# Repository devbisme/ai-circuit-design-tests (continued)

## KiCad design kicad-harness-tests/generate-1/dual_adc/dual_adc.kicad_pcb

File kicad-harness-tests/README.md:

# kicad-harness — tests

## Tool under test

[kicad-harness](https://github.com/zxkmm/kicad-harness) is an Agent Skill plus a Python CLI, `kh`.
It has no MCP server and no LLM of its own; Claude Code reads the skill and runs `kh` from Bash.

- **The skill** (`SKILL.md`, `docs/`) sets the working rules: look up every library id, render
  every placement and look at the PNG, write schematics as `.kicad_sch` text, check with
  DRC/ERC, and generate missing footprints from datasheets. It also tells the agent to fix,
  commit and push the skill repo itself when it finds something wrong.
- **`kh`**, all output JSON:
  - Libraries: `sym` (search, pin numbers/coordinates, raw symbol body), `fp`, `validate`.
  - Queries: `info`, `ls` (positions, bounding boxes), `nets`, `netlist`, `bom`.
  - Renders: `view` (any board region or layer set → PNG), `sview` (schematic sheets → PNG).
  - Checks: `drc` (grouped by type, optional zone refill, schematic parity), `erc`.
  - Generation: `board-from-netlist` (netlist → `.kicad_pcb` with footprints and nets,
    headless), `place` (move footprints in the file), `outline` (rectangular Edge.Cuts).
  - Live (KiCad IPC): `live`, `exec <script.py>` (run kipy scripts against an open PCB editor).
- **Footprints from datasheets** are a documented procedure (`docs/footprints/`) using
  KiCad's wizard templates, not a command.
- **Not included:** a schematic API (schematics are text), an autorouter (the skill documents
  the Specctra DSN/SES bridge to an external router), and ratsnest in renders.

It can both create designs (schematic authoring recipes, `board-from-netlist`, `place`,
`outline`, footprint generation; the README's demo is a TP4056 charger built from scratch) and
review them (`drc`, `erc`, `netlist`, `nets`, `view`/`sview`; "Review your design" is one of
its stated uses). So it is tested as a **hybrid**.

Installation is described in [`setup.md`](setup.md).

- **Version:** commit db4bcdb (2026-10-11), package version 0.1.0, kicad-python 0.8.0.
- **Model:** Claude Opus 5.5 on a Claude Pro plan, Claude Code v2.1.296 (both runs).
- **Backend:** KiCad 10.0.4 (`~/bin/kicad10-root`: `kicad-cli` and the bundled Python 3.11
  `pcbnew`). Library lookups resolve to the KiCad 9.0.9 libraries in `/usr/share/kicad`
  (see `setup.md`).

## Why this tool

- It is a different shape from the MCP servers tested so far: a skill plus a CLI that Claude
  drives from Bash, with no tool-call schema in between.
- It gives the agent eyes: `view`/`sview` render any board region or sheet to a PNG that the
  agent is told to look at after every placement.
- `board-from-netlist`, `place` and `outline` cover the schematic → PCB step headlessly, which
  most of the other tools needed the KiCad GUI for.

## Runs

| Run | What it tests | Prompts | Outcome | Equiv. API cost | Time |
|---|---|---|---|---|---|
| [`analyze-1`](analyze-1/) | **Analysis** and JLCPCB fab outputs for an existing design (Konnect run 2) | 1 (multi-part, [`analysis_prompt.txt`](analyze-1/analysis_prompt.txt)) | ERC 0 errors, DRC 0 errors; 14 ranked findings; Gerbers, BOM, CPL, PNG. Found a `kh drc --refill` bug that reports 856 false violations | $3.02 | ~9 min |
| [`generate-1`](generate-1/) | A **full design** from the dual-ADC requirements | 1, plus 4 "keep going" while Freerouting ran ([`design_prompt.txt`](generate-1/design_prompt.txt)) | 6-sheet schematic and routed 4-layer board. ERC 0 errors, DRC 0 errors / 0 unconnected / 0 parity | $10.87 | ~1 h wall clock (~46 min of Claude working time) |

Each run directory has an `executive_summary.md`; start there. Costs are the equivalent
first-party API price of the tokens used (`claude_cost.txt`), not what the Pro subscription
billed. The findings in both runs have not yet been validated by hand.

### analyze-1: analyzer on an existing design

The input is the KiCad project produced by
[Konnect run 2](../konnect-tests/dual-adc-usb-2/): a 4-layer, 140 × 90 mm dual-channel 12-bit,
10 MS/s ADC board with a USB 2.0 interface (LTC2290 ADC, iCE40HX4K FPGA, SDRAM, FT2232H).
The `.kicad_*` files are unchanged copies; the run checked the board's md5 before and after.
The other tools' analysis runs used the same design.

Prompt: `do what analysis-prompt.txt says.` ([`analysis_prompt.txt`](analyze-1/analysis_prompt.txt)
asks for a design review, JLCPCB Gerbers, BOM and CPL, a dark-gray PCB PNG and an executive
summary.)

Quick look:

- **Checks:** `kh drc` gave 0 errors, 0 unconnected, clean schematic parity and 343 warnings.
  `kh erc` gave 0 errors; 201 of its warnings are a stale global library table and 2 are
  benign pin-type warnings.
- **Review method:** every sheet rendered with `kh sview` and read, `kh netlist` plus a
  pin-by-pin dump of every IC, `kh view` renders, and pcbnew scripts for decoupling distance,
  via-in-pad, layer use, pair lengths and stackup. Three datasheets/app notes were fetched and
  cited (FTDI AN_130, TI LM27762, ADA4817).
- **Findings (14, ranked):**
  - Assembly: no LCSC/MPN fields in the BOM; CPL rotations unverified; four through-hole parts.
  - Architecture: FT2232H channel B (the FPGA flash path) is dead while channel A runs sync
    FIFO; the LM27762 divider values check out but R406/R408 are just under the 50 kΩ minimum
    and PGOOD floats; likely over the USB suspend-current limit.
  - Layout: FPGA decaps 6–18 mm from their pins; the AFE sits over the digital +3V3 plane;
    the charge pump sits between the two AFE channels; 9 vias in the ADC's exposed pad;
    no stackup or net classes, so USB D+/D− impedance is uncontrolled; silkscreen overlaps.
  - A list of items that were checked and found correct (divider compensation, gain chain,
    VOCM, clock pins, VBUS capacitance, etc.).
- **Outputs:** `kh` has no fab export, so Gerbers, drill and CPL came from `kicad-cli` 10; the
  BOM came from `kh bom`. All are reformatted for JLCPCB in `analyze-1/jlcpcb/`.
- **kicad-harness problems found:**
  - `kh drc --refill` copies only `.kicad_pcb` and `.kicad_pro` to a temp directory, so the
    project's `.kicad_dru` rules are lost. Result: 856 false violations (499 clearance, 14
    track width). The skill says to "always use --refill".
  - ERC JSON coordinates are 100× too small (passed through from kicad-cli 10 unscaled).
  - `rsvg-convert` is not installed, so `view`/`sview` fail; an Inkscape shim in the
    scratchpad stood in.
- **Not done on purpose:** SKILL.md tells the agent to commit and push fixes to the skill
  repo. Claude didn't, because the user's rules require permission for any git action.

### generate-1: full design

The prompt is [`design_prompt.txt`](generate-1/design_prompt.txt), identical to the one used
for the other tools' design runs.

Prompts, in sequence in one session:

```
do what design_prompt.txt says.
```
```
keep going        (x4)
```

Claude ended its turn each time it was waiting on Freerouting in the background, so the
"keep going" prompts were needed to make it check progress. It then killed and relaunched
the router with fewer passes and finished the last 12 connections with its own A* router.

Quick look:

- **Design:**
  - Signal path: BNC → 1 MΩ‖15 pF 10:1 compensated attenuator → clamp → OPA810 buffer →
    THS4521 FDA (gain 0.95) → single-pole RC anti-alias filter (4.8 MHz) → LTC2290.
  - Capture and link: iCE40HX4K-TQ144 with an 8 MB IS42S16400J SDRAM (0.2 s at full rate,
    twice the requirement); FT232H in sync-245 FIFO mode; W25Q32 config flash.
  - Power: USB-B, about 256 mA estimated, so USB-C wasn't needed. TLV62569 buck (3.3 V),
    LP5907 (3.0 V), AP2112 (1.2 V), TPS60403 (−5 V).
  - Decisions with options are in the executive summary.
- **Schematic:** root plus 6 sheets (Power, FrontEnd, ADC, FPGA, Memory, USB), 163 parts,
  176 nets.
  - Written as label-based `.kicad_sch` text by Claude's `gen_sch.py` from a Python netlist
    (`design.py`); every symbol, footprint and pin number was looked up with `kh sym --pins`
    and `kh validate`.
  - The kicad-cli netlist matches `design.py` exactly. ERC: 0 errors, 2 warnings (FT232H
    symbol pin types).
- **PCB:** 120 × 88 mm, 4 layers: In1 GND plane, In2 +3V3 plane, signals on F/B.Cu.
  - `kh board-from-netlist` created the board. Claude's scripts did placement (anchors,
    FPGA pin swapping by angle with the pin map fed back to the schematic, greedy decap
    placement), net classes, plane zones and 196 locked fanout vias.
  - Freerouting 2.4.1 on a DSN with the plane nets removed left 12 unrouted; a small grid A*
    (`fix_route.py`) finished them. One net uses a short run on the In2 plane layer.
  - DRC (kicad-cli 10, refilled): 0 errors, 0 unconnected, 0 parity issues, 41 warnings.
  - Track minimum was relaxed to 0.10 mm because Freerouting necked some tracks.
- **Not ready for fab:**
  - FTDI, ADI and Lattice datasheets couldn't be downloaded, so FT232H, LTC2290 and iCE40
    pin wiring is from memory and is labelled that way.
  - ~250 mA draw before USB configuration (limit 100 mA); no load switch on PWREN#.
  - Single-pole anti-aliasing; USB D+/D− not routed as a 90 Ω pair; SDRAM bus not
    length-matched; fixed (not trimmable) probe compensation.
  - No FPGA gateware or host software.
- **kicad-harness / environment problems found:**
  - `kh` library lookups fell back to KiCad 9 libraries, where the USB-B shield pad is named
    `5` instead of `SH`. Fixed with project `sym-lib-table`/`fp-lib-table` files.
  - `rsvg-convert` missing (same Inkscape shim as run 1).
  - KiCad 10 pcbnew SWIG: `BOARD.Tracks()` breaks after `Remove()`, and removing Edge.Cuts
    drawings segfaults.
  - No autorouter in `kh`; the DSN/SES bridge to Freerouting is documented but scripted by
    Claude.
- **Not done on purpose:** no commits to the skill repo, as in run 1.

### Comparison of the two runs

- `kh` did most of the inspection and checking work in both runs, but Claude wrote 16
  Python scripts to do the actual design: schematic writing, placement, routing prep and route
  completion. kicad-harness is closer to a set of instruments than to a design tool.
- The skill's "render it and look" rule was followed in both runs and was useful for
  reviewing placement.
- Both runs found real `kh` bugs (`--refill` losing `.kicad_dru`, ERC coordinate scale) and
  environment gaps that the tool doesn't check for (`rsvg-convert`, stale library tables).

## Layout

```
kicad-harness-tests/
├── README.md                   <- this file
├── setup.md                    <- how kicad-harness was installed and configured
├── analyze-1/                  <- run 1: analysis of the Konnect run-2 design
│   ├── executive_summary.md    <- start here
│   ├── analysis_prompt.txt     <- the prompt
│   ├── claude_transcript.txt   <- the session
│   ├── claude_cost.txt         <- token usage and equivalent API cost
│   ├── session_cost.py         <- script that produced claude_cost.txt
│   ├── dual_adc_usb.kicad_pro, .kicad_pcb, .kicad_dru, .kicad_prl, .kicad_sch
│   ├── afe_a, afe_b, adc, fpga, usb, power .kicad_sch
│   ├── dual_adc_usb_pcb.png    <- PCB render on a dark-gray background
│   └── jlcpcb/                 <- Gerber zip, unzipped gerbers, JLCPCB BOM and CPL
└── generate-1/                 <- run 2: full design from the dual-ADC prompt
    ├── executive_summary.md    <- start here
    ├── design_prompt.txt       <- the prompt
    ├── claude_transcript.txt   <- the session
    ├── claude_cost.txt         <- token usage and equivalent API cost
    ├── session_cost.py         <- script that produced claude_cost.txt
    ├── dual_adc/               <- the KiCad 10 project
    │   ├── dual_adc.kicad_pro, .kicad_pcb, .kicad_prl, .kicad_sch
    │   ├── Power, FrontEnd, ADC, FPGA, Memory, USB .kicad_sch
    │   ├── sym-lib-table, fp-lib-table  <- point at the KiCad 10 libraries
    │   ├── fab/                <- Gerbers, drill, pick-and-place, BOM, schematic PDF
    │   └── renders/            <- board front/back and schematic sheet PNGs
    ├── work/                   <- intermediate boards, DSN/SES, Freerouting log, DRC/ERC
    │                              JSON, renders
    └── scripts/
        ├── circuit.py          <- small netlist DSL (parts, pin->net maps, sheets)
        ├── design.py           <- the netlist: parts, values, footprints, pin->net
        ├── pins.py             <- symbol pin dump via `kh sym --pins`
        ├── pins10.py, fpinfo.py  <- pin and pad dumps read straight from the KiCad 10 libraries
        ├── sexp.py             <- small S-expression reader/writer
        ├── gen_sch.py          <- writes the label-based hierarchical schematic
        ├── verify_netlist.py   <- kicad-cli netlist vs design.py
        ├── place.py, pinmap.json  <- placement and FPGA pin reassignment
        ├── route_prep.py       <- net classes, plane zones, locked fanout, DSN export
        ├── edit_fanout.py      <- one-off fix to a bad GND fanout at U10
        ├── dsn_cut.py          <- removes plane nets from the DSN
        ├── import_ses.py       <- Freerouting SES import, pour refill
        ├── fix_route.py        <- grid A* for the connections Freerouting left
        └── prune.py, polish.py <- dead-end spur removal; outline, holes, silk
```

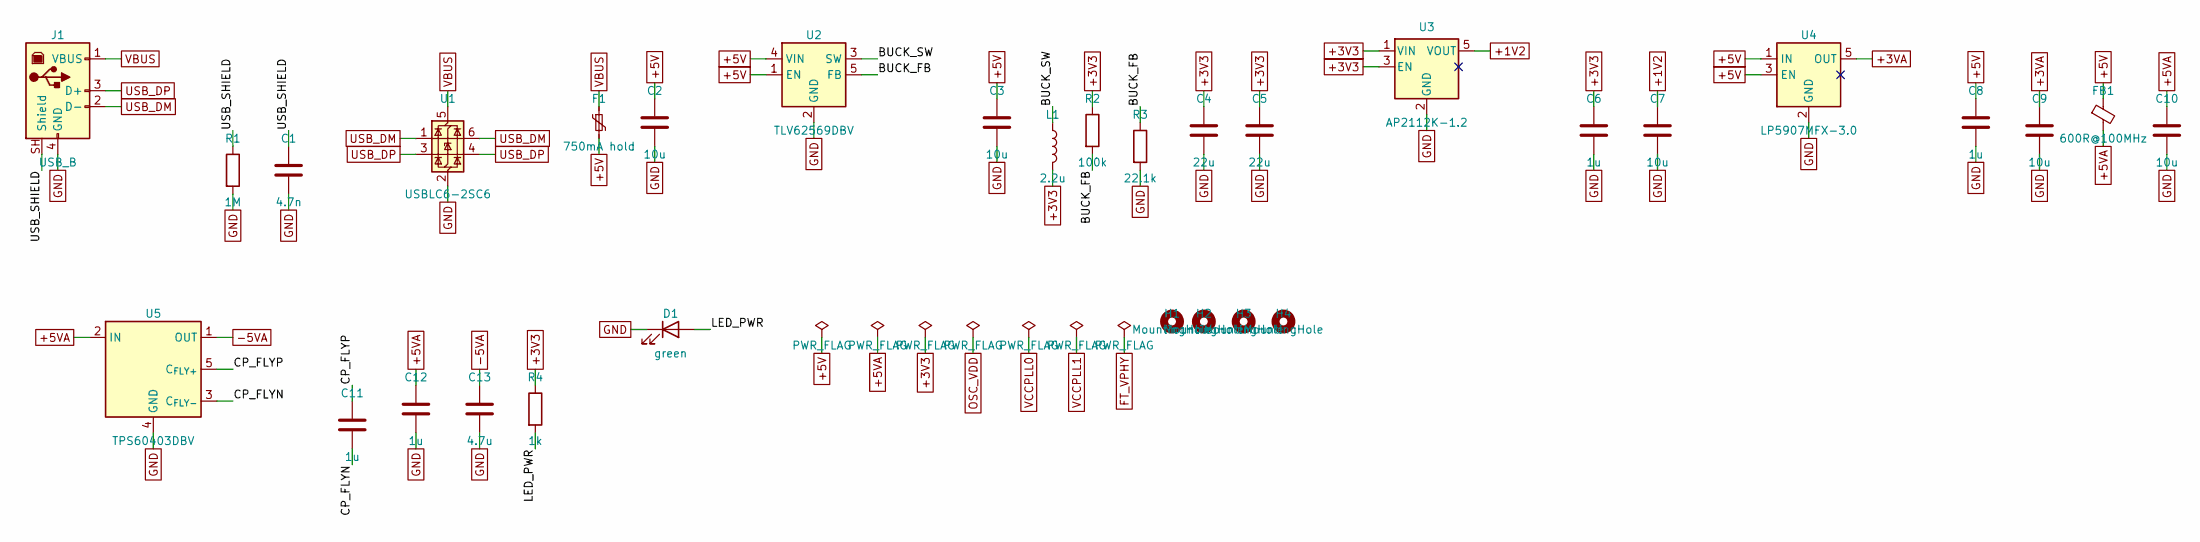
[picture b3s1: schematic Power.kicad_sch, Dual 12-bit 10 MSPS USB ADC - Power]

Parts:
C1: 4.7n; C_0805_2012Metric
C2, C3, C7, C9, C10: 10u; C_0805_2012Metric
C4, C5: 22u; C_0805_2012Metric
C6, C8, C11, C12: 1u; C_0603_1608Metric
C13: 4.7u; C_0805_2012Metric
D1: green; LED_0603_1608Metric
F1: 750mA hold; Fuse_1206_3216Metric
FB1: 600R@100MHz; L_0805_2012Metric
H1, H2, H3, H4: MountingHole; MountingHole_3.2mm_M3
J1: USB_B; USB_B_OST_USB-B1HSxx_Horizontal
L1: 2.2u; L_Bourns-SRN4018
R1: 1M; R_0603_1608Metric
R2: 100k; R_0603_1608Metric
R3: 22.1k; R_0603_1608Metric
R4: 1k; R_0603_1608Metric
U1: USBLC6-2SC6; SOT-23-6
U2: TLV62569DBV; SOT-23-5
U3: AP2112K-1.2; SOT-23-5
U4: LP5907MFX-3.0; SOT-23-5
U5: TPS60403DBV; SOT-23-5

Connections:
+1V2: C7.1, U3.5 (VOUT); also elsewhere on the board
+3V3: C4.1, C5.1, C6.1, L1.2, R2.1, R4.1, U3.1 (VIN), U3.3 (EN); also elsewhere on the board
+3VA: C9.1, U4.5 (OUT); also elsewhere on the board
+5V: C2.1, C3.1, C8.1, F1.2, FB1.1, U2.1 (EN), U2.4 (VIN), U4.1 (IN), U4.3 (EN)
+5VA: C10.1, C12.1, FB1.2, U5.2 (IN); also elsewhere on the board
-5VA: C13.1, U5.1 (OUT); also elsewhere on the board
/Power/BUCK_FB: R2.2, R3.1, U2.5 (FB)
/Power/BUCK_SW: L1.1, U2.3 (SW)
/Power/CP_FLYN: C11.2, U5.3 (C_{FLY-})
/Power/CP_FLYP: C11.1, U5.5 (C_{FLY+})
/Power/LED_PWR: D1.2 (A), R4.2
/Power/USB_SHIELD: C1.1, J1.SH (Shield), R1.1
GND: C1.2, C2.2, C3.2, C4.2, C5.2, C6.2, C7.2, C8.2, C9.2, C10.2, C12.2, C13.2, D1.1 (K), J1.4 (GND), R1.2, R3.2, U1.2 (GND), U2.2 (GND), U3.2 (GND), U4.2 (GND), U5.4 (GND); also elsewhere on the board
USB_DM: J1.2 (D-), U1.1 (I/O1), U1.6 (I/O1); also elsewhere on the board
USB_DP: J1.3 (D+), U1.3 (I/O2), U1.4 (I/O2); also elsewhere on the board
VBUS: F1.1, J1.1 (VBUS), U1.5 (VBUS)

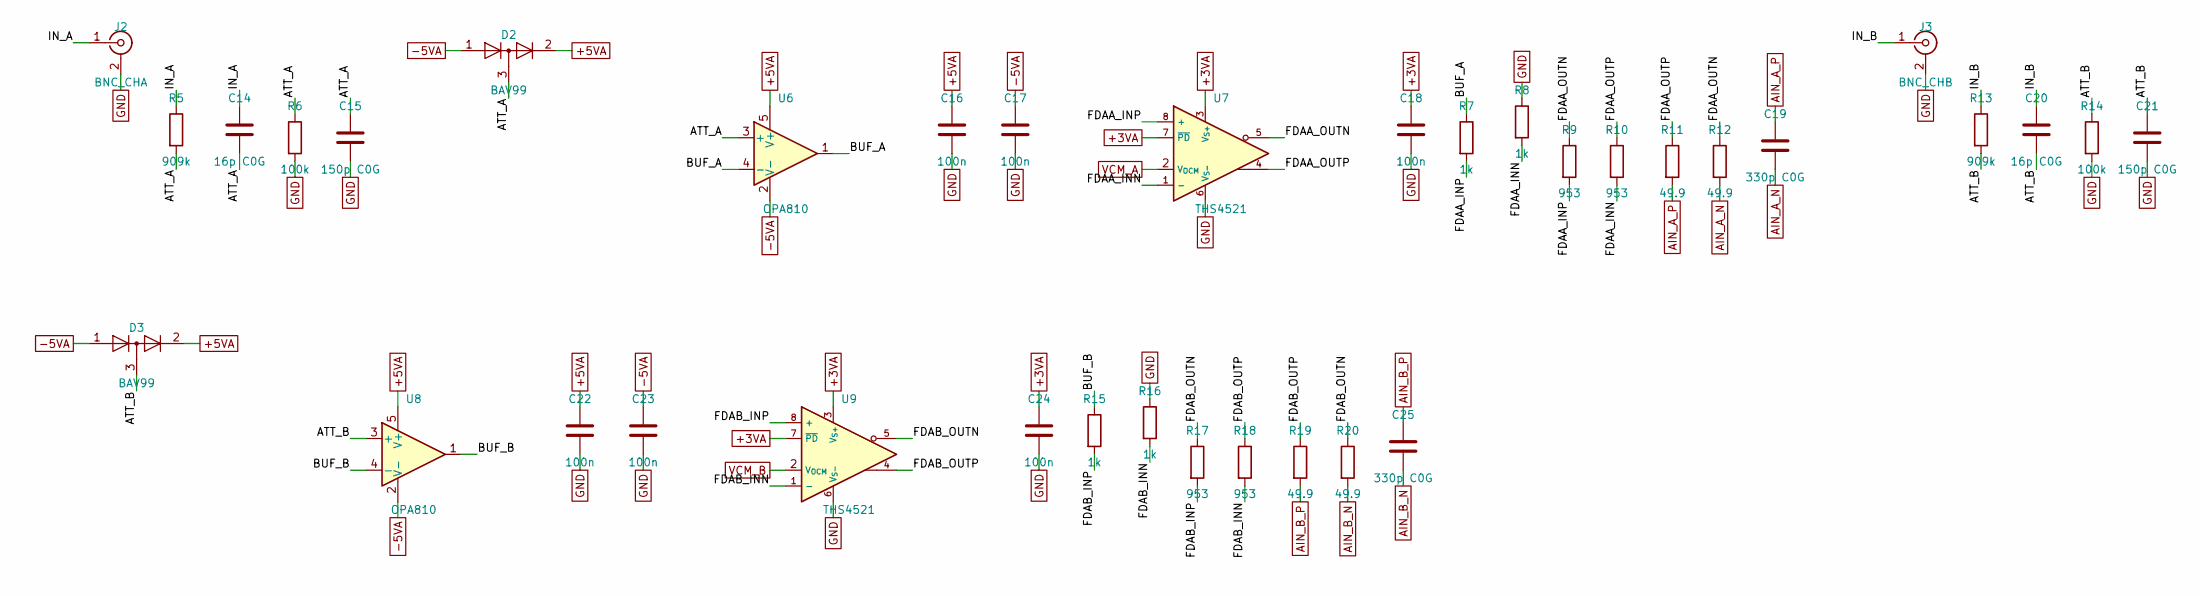
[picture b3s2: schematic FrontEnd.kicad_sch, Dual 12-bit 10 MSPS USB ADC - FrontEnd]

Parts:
C14, C20: 16p C0G; C_1206_3216Metric
C15, C21: 150p C0G; C_0603_1608Metric
C16, C17, C18, C22, C23, C24: 100n; C_0603_1608Metric
C19, C25: 330p C0G; C_0603_1608Metric
D2, D3: BAV99; SOT-23
J2: BNC_CHA; BNC_Amphenol_B6252HB-NPP3G-50_Horizontal
J3: BNC_CHB; BNC_Amphenol_B6252HB-NPP3G-50_Horizontal
R5, R13: 909k; R_1206_3216Metric
R6, R14: 100k; R_0603_1608Metric
R7, R8, R15, R16: 1k; R_0603_1608Metric
R9, R10, R17, R18: 953; R_0603_1608Metric
R11, R12, R19, R20: 49.9; R_0603_1608Metric
U6, U8: OPA810; SOT-23-5
U7, U9: THS4521; SOIC-8_3.9x4.9mm_P1.27mm

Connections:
+3VA: C18.1, C24.1, U7.3 (V_{S+}), U7.7 (~PD), U9.3 (V_{S+}), U9.7 (~PD); also elsewhere on the board
+5VA: C16.1, C22.1, D2.2 (A), D3.2 (A), U6.5 (V+), U8.5 (V+); also elsewhere on the board
-5VA: C17.1, C23.1, D2.1 (K), D3.1 (K), U6.2 (V-), U8.2 (V-); also elsewhere on the board
/FrontEnd/ATT_A: C14.2, C15.1, D2.3 (K), R5.2, R6.1, U6.3 (+)
/FrontEnd/ATT_B: C20.2, C21.1, D3.3 (K), R13.2, R14.1, U8.3 (+)
/FrontEnd/BUF_A: R7.1, U6.1, U6.4 (-)
/FrontEnd/BUF_B: R15.1, U8.1, U8.4 (-)
/FrontEnd/FDAA_INN: R8.2, R10.2, U7.1 (-)
/FrontEnd/FDAA_INP: R7.2, R9.2, U7.8 (+)
/FrontEnd/FDAA_OUTN: R9.1, R12.1, U7.5
/FrontEnd/FDAA_OUTP: R10.1, R11.1, U7.4
/FrontEnd/FDAB_INN: R16.2, R18.2, U9.1 (-)
/FrontEnd/FDAB_INP: R15.2, R17.2, U9.8 (+)
/FrontEnd/FDAB_OUTN: R17.1, R20.1, U9.5
/FrontEnd/FDAB_OUTP: R18.1, R19.1, U9.4
/FrontEnd/IN_A: C14.1, J2.1 (In), R5.1
/FrontEnd/IN_B: C20.1, J3.1 (In), R13.1
AIN_A_N: C19.2, R12.2; also elsewhere on the board
AIN_A_P: C19.1, R11.2; also elsewhere on the board
AIN_B_N: C25.2, R20.2; also elsewhere on the board
AIN_B_P: C25.1, R19.2; also elsewhere on the board
GND: C15.2, C16.2, C17.2, C18.2, C21.2, C22.2, C23.2, C24.2, J2.2 (Ext), J3.2 (Ext), R6.2, R8.1, R14.2, R16.1, U7.6 (V_{S-}), U9.6 (V_{S-}); also elsewhere on the board
VCM_A: U7.2 (V_{OCM}); also elsewhere on the board
VCM_B: U9.2 (V_{OCM}); also elsewhere on the board

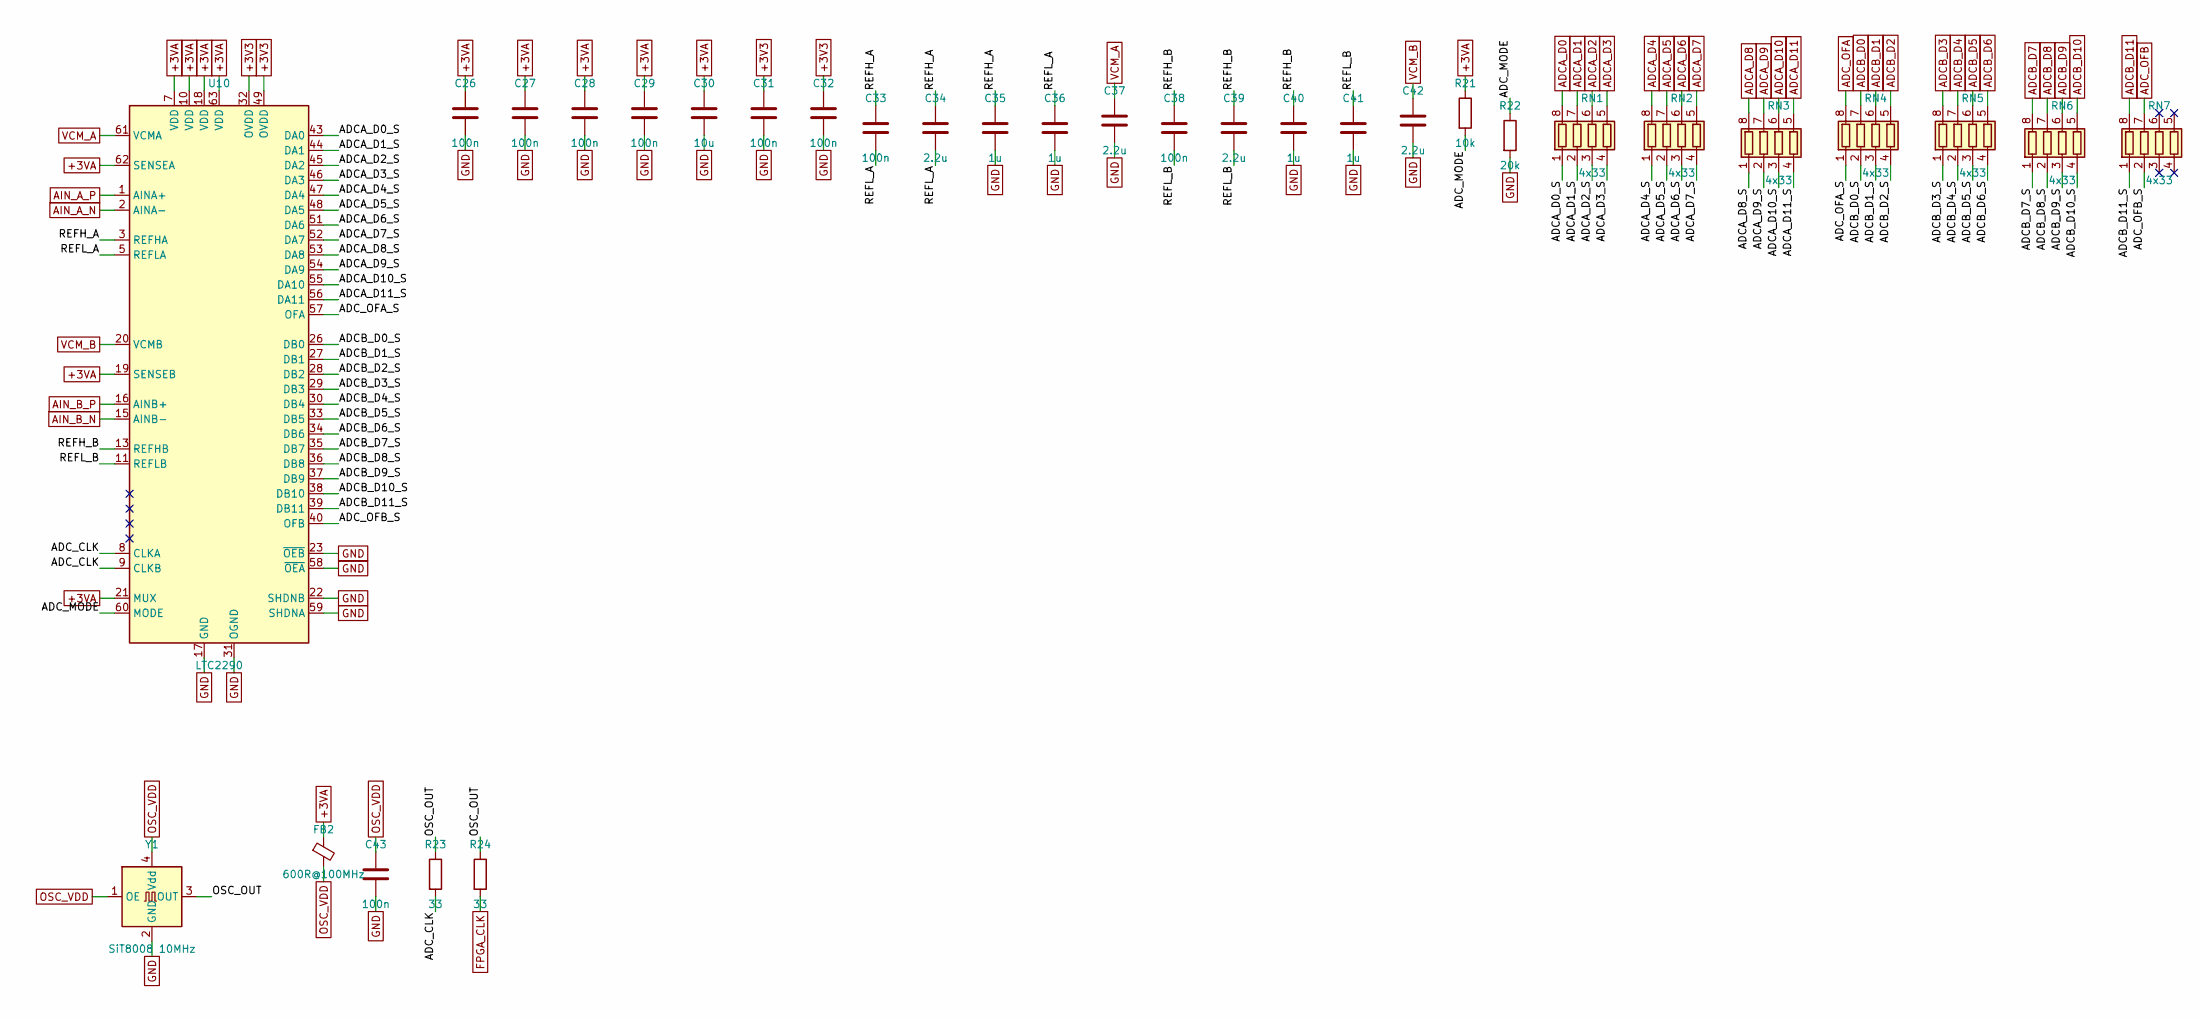
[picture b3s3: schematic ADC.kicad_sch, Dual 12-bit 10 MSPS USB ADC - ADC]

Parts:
C26, C27, C28, C29, C31, C32, C33, C38, C43: 100n; C_0603_1608Metric
C30: 10u; C_0805_2012Metric
C34, C37, C39, C42: 2.2u; C_0603_1608Metric
C35, C36, C40, C41: 1u; C_0603_1608Metric
FB2: 600R@100MHz; L_0805_2012Metric
R21: 10k; R_0603_1608Metric
R22: 20k; R_0603_1608Metric
R23, R24: 33; R_0603_1608Metric
RN1, RN2, RN3, RN4, RN5, RN6, RN7: 4x33; R_Array_Convex_4x0603
U10: LTC2290; QFN-64-1EP_9x9mm_P0.5mm_EP7.15x7.15mm
Y1: SiT8008 10MHz; Oscillator_SMD_SiT_PQFN-4Pin_3.2x2.5mm

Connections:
+3V3: C31.1, C32.1, U10.32 (OVDD), U10.49 (OVDD); also elsewhere on the board
+3VA: C26.1, C27.1, C28.1, C29.1, C30.1, FB2.1, R21.1, U10.7 (VDD), U10.10 (VDD), U10.18 (VDD), U10.19 (SENSEB), U10.21 (MUX), U10.62 (SENSEA), U10.63 (VDD); also elsewhere on the board
/ADC/ADCA_D0_S: RN1.1 (R1.1), U10.43 (DA0)
/ADC/ADCA_D1_S: RN1.2 (R2.1), U10.44 (DA1)
/ADC/ADCA_D2_S: RN1.3 (R3.1), U10.45 (DA2)
/ADC/ADCA_D3_S: RN1.4 (R4.1), U10.46 (DA3)
/ADC/ADCA_D4_S: RN2.1 (R1.1), U10.47 (DA4)
/ADC/ADCA_D5_S: RN2.2 (R2.1), U10.48 (DA5)
/ADC/ADCA_D6_S: RN2.3 (R3.1), U10.51 (DA6)
/ADC/ADCA_D7_S: RN2.4 (R4.1), U10.52 (DA7)
/ADC/ADCA_D8_S: RN3.1 (R1.1), U10.53 (DA8)
/ADC/ADCA_D9_S: RN3.2 (R2.1), U10.54 (DA9)
/ADC/ADCA_D10_S: RN3.3 (R3.1), U10.55 (DA10)
/ADC/ADCA_D11_S: RN3.4 (R4.1), U10.56 (DA11)
/ADC/ADCB_D0_S: RN4.2 (R2.1), U10.26 (DB0)
/ADC/ADCB_D1_S: RN4.3 (R3.1), U10.27 (DB1)
/ADC/ADCB_D2_S: RN4.4 (R4.1), U10.28 (DB2)
/ADC/ADCB_D3_S: RN5.1 (R1.1), U10.29 (DB3)
/ADC/ADCB_D4_S: RN5.2 (R2.1), U10.30 (DB4)
/ADC/ADCB_D5_S: RN5.3 (R3.1), U10.33 (DB5)
/ADC/ADCB_D6_S: RN5.4 (R4.1), U10.34 (DB6)
/ADC/ADCB_D7_S: RN6.1 (R1.1), U10.35 (DB7)
/ADC/ADCB_D8_S: RN6.2 (R2.1), U10.36 (DB8)
/ADC/ADCB_D9_S: RN6.3 (R3.1), U10.37 (DB9)
/ADC/ADCB_D10_S: RN6.4 (R4.1), U10.38 (DB10)
/ADC/ADCB_D11_S: RN7.1 (R1.1), U10.39 (DB11)
/ADC/ADC_CLK: R23.2, U10.8 (CLKA), U10.9 (CLKB)
/ADC/ADC_MODE: R21.2, R22.1, U10.60 (MODE)
/ADC/ADC_OFA_S: RN4.1 (R1.1), U10.57 (OFA)
/ADC/ADC_OFB_S: RN7.2 (R2.1), U10.40 (OFB)
/ADC/OSC_OUT: R23.1, R24.1, Y1.3 (OUT)
/ADC/REFH_A: C33.1, C34.1, C35.1, U10.3 (REFHA), U10.4 (REFHA)
/ADC/REFH_B: C38.1, C39.1, C40.1, U10.13 (REFHB), U10.14 (REFHB)
/ADC/REFL_A: C33.2, C34.2, C36.1, U10.5 (REFLA), U10.6 (REFLA)
/ADC/REFL_B: C38.2, C39.2, C41.1, U10.11 (REFLB), U10.12 (REFLB)
ADCA_D0: RN1.8 (R1.2); also elsewhere on the board
ADCA_D1: RN1.7 (R2.2); also elsewhere on the board
ADCA_D2: RN1.6 (R3.2); also elsewhere on the board
ADCA_D3: RN1.5 (R4.2); also elsewhere on the board
ADCA_D4: RN2.8 (R1.2); also elsewhere on the board
ADCA_D5: RN2.7 (R2.2); also elsewhere on the board
ADCA_D6: RN2.6 (R3.2); also elsewhere on the board
ADCA_D7: RN2.5 (R4.2); also elsewhere on the board
ADCA_D8: RN3.8 (R1.2); also elsewhere on the board
ADCA_D9: RN3.7 (R2.2); also elsewhere on the board
ADCA_D10: RN3.6 (R3.2); also elsewhere on the board
ADCA_D11: RN3.5 (R4.2); also elsewhere on the board
ADCB_D0: RN4.7 (R2.2); also elsewhere on the board
ADCB_D1: RN4.6 (R3.2); also elsewhere on the board
ADCB_D2: RN4.5 (R4.2); also elsewhere on the board
ADCB_D3: RN5.8 (R1.2); also elsewhere on the board
ADCB_D4: RN5.7 (R2.2); also elsewhere on the board
ADCB_D5: RN5.6 (R3.2); also elsewhere on the board
ADCB_D6: RN5.5 (R4.2); also elsewhere on the board
ADCB_D7: RN6.8 (R1.2); also elsewhere on the board
ADCB_D8: RN6.7 (R2.2); also elsewhere on the board
ADCB_D9: RN6.6 (R3.2); also elsewhere on the board
ADCB_D10: RN6.5 (R4.2); also elsewhere on the board
ADCB_D11: RN7.8 (R1.2); also elsewhere on the board
ADC_OFA: RN4.8 (R1.2); also elsewhere on the board
ADC_OFB: RN7.7 (R2.2); also elsewhere on the board
AIN_A_N: U10.2 (AINA-); also elsewhere on the board
AIN_A_P: U10.1 (AINA+); also elsewhere on the board
AIN_B_N: U10.15 (AINB-); also elsewhere on the board
AIN_B_P: U10.16 (AINB+); also elsewhere on the board
FPGA_CLK: R24.2; also elsewhere on the board
GND: C26.2, C27.2, C28.2, C29.2, C30.2, C31.2, C32.2, C35.2, C36.2, C37.2, C40.2, C41.2, C42.2, C43.2, R22.2, U10.17 (GND), U10.22 (SHDNB), U10.23 (~OEB), U10.31 (OGND), U10.50 (OGND), U10.58 (~OEA), U10.59 (SHDNA), U10.64 (GND), U10.65 (GND), Y1.2 (GND); also elsewhere on the board
OSC_VDD: C43.1, FB2.2, Y1.1 (OE), Y1.4 (Vdd)
VCM_A: C37.1, U10.61 (VCMA); also elsewhere on the board
VCM_B: C42.1, U10.20 (VCMB); also elsewhere on the board

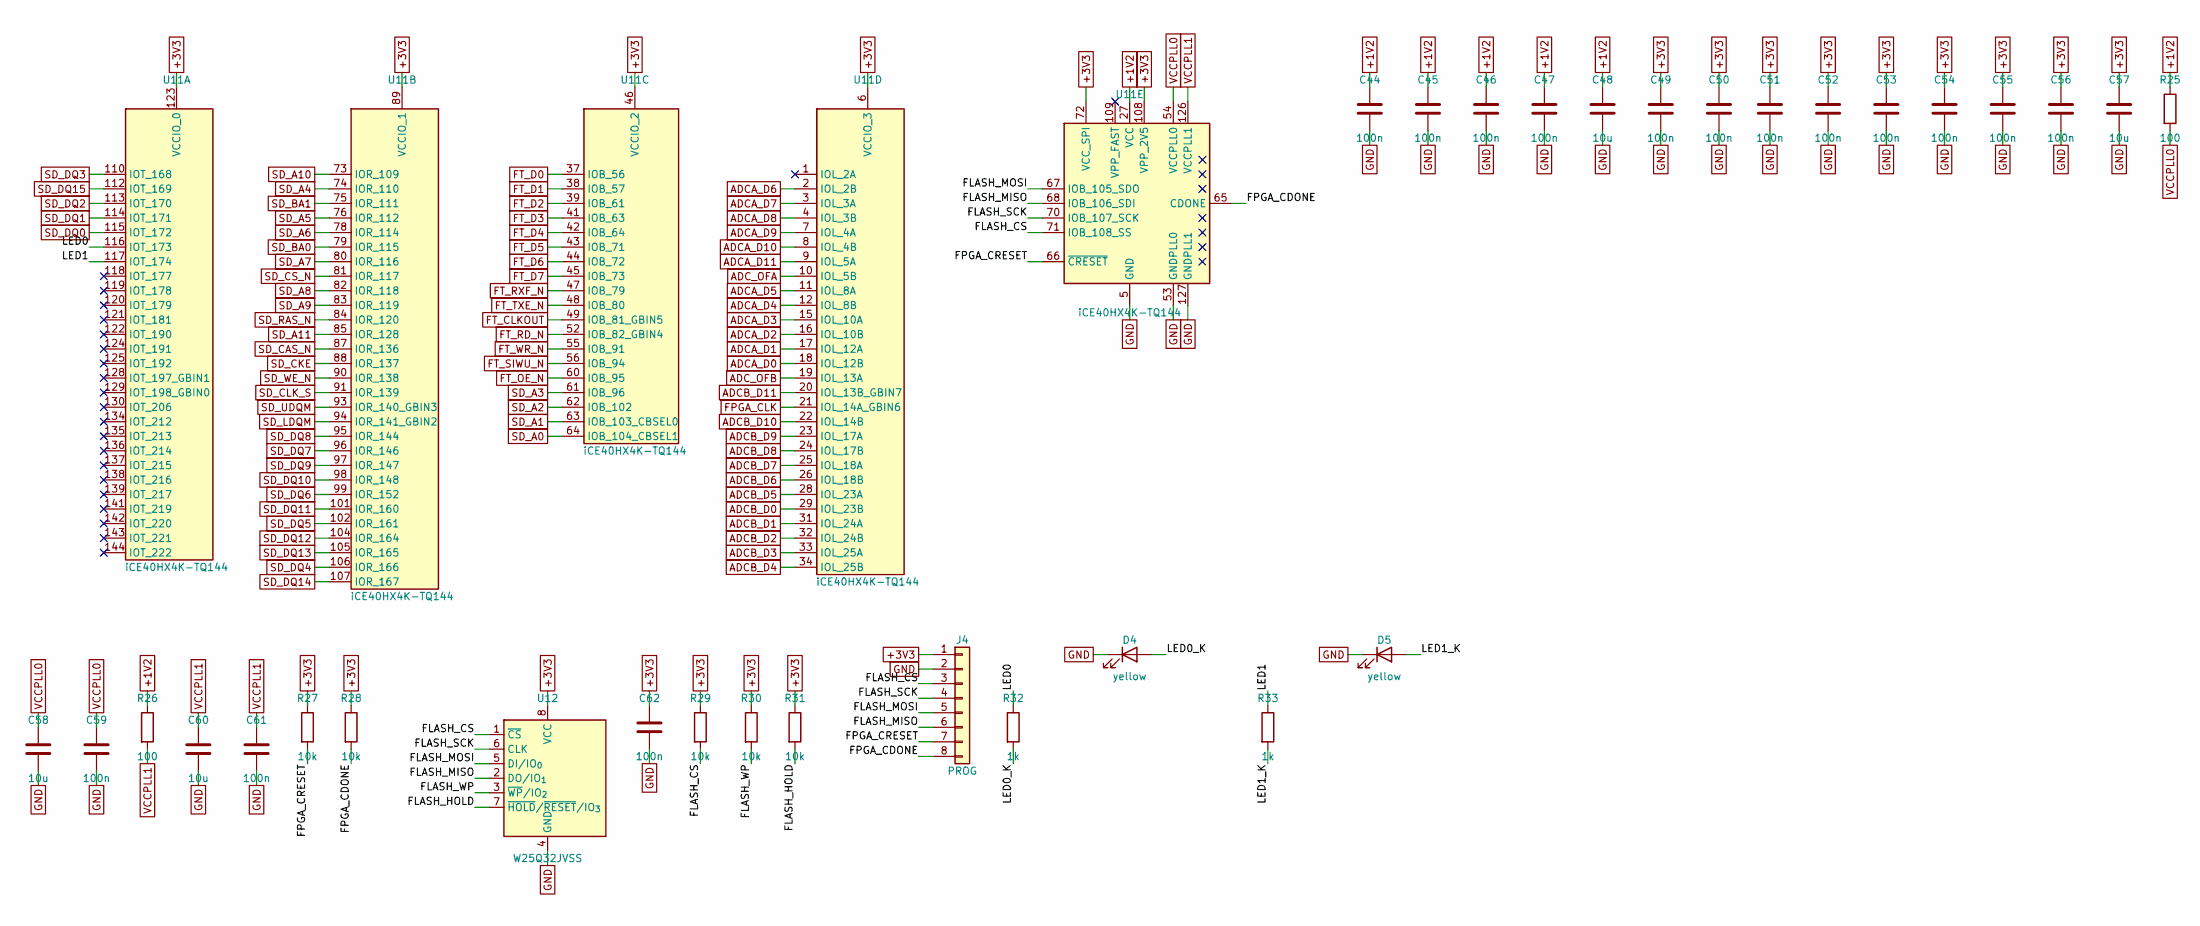
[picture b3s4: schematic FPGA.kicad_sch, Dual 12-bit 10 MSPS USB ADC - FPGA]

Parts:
C44, C45, C46, C47, C49, C50, C51, C52, C53, C54, C55, C56, C59, C61, C62: 100n; C_0603_1608Metric
C48, C57, C58, C60: 10u; C_0805_2012Metric
D4, D5: yellow; LED_0603_1608Metric
J4: PROG; PinHeader_1x08_P2.54mm_Vertical
R25, R26: 100; R_0603_1608Metric
R27, R28, R29, R30, R31: 10k; R_0603_1608Metric
R32, R33: 1k; R_0603_1608Metric
U11: iCE40HX4K-TQ144; TQFP-144_20x20mm_P0.5mm
U12: W25Q32JVSS; SOIC-8_5.3x5.3mm_P1.27mm

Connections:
+1V2: C44.1, C45.1, C46.1, C47.1, C48.1, R25.1, R26.1, U11.27 (VCC), U11.40 (VCC), U11.92 (VCC), U11.111 (VCC); also elsewhere on the board
+3V3: C49.1, C50.1, C51.1, C52.1, C53.1, C54.1, C55.1, C56.1, C57.1, C62.1, J4.1, R27.1, R28.1, R29.1, R30.1, R31.1, U11.6 (VCCIO_3), U11.30 (VCCIO_3), U11.46 (VCCIO_2), U11.57 (VCCIO_2), U11.72 (VCC_SPI), U11.89 (VCCIO_1), U11.100 (VCCIO_1), U11.108 (VPP_2V5), U11.123 (VCCIO_0), U11.131 (VCCIO_0), U12.8 (VCC); also elsewhere on the board
/FPGA/FLASH_CS: J4.3, R29.2, U11.71 (IOB_108_SS), U12.1 (~CS)
/FPGA/FLASH_HOLD: R31.2, U12.7 (~HOLD/~RESET/IO_{3})
/FPGA/FLASH_MISO: J4.6, U11.68 (IOB_106_SDI), U12.2 (DO/IO_{1})
/FPGA/FLASH_MOSI: J4.5, U11.67 (IOB_105_SDO), U12.5 (DI/IO_{0})
/FPGA/FLASH_SCK: J4.4, U11.70 (IOB_107_SCK), U12.6 (CLK)
/FPGA/FLASH_WP: R30.2, U12.3 (~WP/IO_{2})
/FPGA/FPGA_CDONE: J4.8, R28.2, U11.65 (CDONE)
/FPGA/FPGA_CRESET: J4.7, R27.2, U11.66 (~CRESET)
/FPGA/LED0: R32.1, U11.116 (IOT_173)
/FPGA/LED0_K: D4.2 (A), R32.2
/FPGA/LED1: R33.1, U11.117 (IOT_174)
/FPGA/LED1_K: D5.2 (A), R33.2
ADCA_D0: U11.18 (IOL_12B); also elsewhere on the board
ADCA_D1: U11.17 (IOL_12A); also elsewhere on the board
ADCA_D2: U11.16 (IOL_10B); also elsewhere on the board
ADCA_D3: U11.15 (IOL_10A); also elsewhere on the board
ADCA_D4: U11.12 (IOL_8B); also elsewhere on the board
ADCA_D5: U11.11 (IOL_8A); also elsewhere on the board
ADCA_D6: U11.2 (IOL_2B); also elsewhere on the board
ADCA_D7: U11.3 (IOL_3A); also elsewhere on the board
ADCA_D8: U11.4 (IOL_3B); also elsewhere on the board
ADCA_D9: U11.7 (IOL_4A); also elsewhere on the board
ADCA_D10: U11.8 (IOL_4B); also elsewhere on the board
ADCA_D11: U11.9 (IOL_5A); also elsewhere on the board
ADCB_D0: U11.29 (IOL_23B); also elsewhere on the board
ADCB_D1: U11.31 (IOL_24A); also elsewhere on the board
ADCB_D2: U11.32 (IOL_24B); also elsewhere on the board
ADCB_D3: U11.33 (IOL_25A); also elsewhere on the board
ADCB_D4: U11.34 (IOL_25B); also elsewhere on the board
ADCB_D5: U11.28 (IOL_23A); also elsewhere on the board
ADCB_D6: U11.26 (IOL_18B); also elsewhere on the board
ADCB_D7: U11.25 (IOL_18A); also elsewhere on the board
ADCB_D8: U11.24 (IOL_17B); also elsewhere on the board
ADCB_D9: U11.23 (IOL_17A); also elsewhere on the board
ADCB_D10: U11.22 (IOL_14B); also elsewhere on the board
ADCB_D11: U11.20 (IOL_13B_GBIN7); also elsewhere on the board
ADC_OFA: U11.10 (IOL_5B); also elsewhere on the board
ADC_OFB: U11.19 (IOL_13A); also elsewhere on the board
FPGA_CLK: U11.21 (IOL_14A_GBIN6); also elsewhere on the board
FT_CLKOUT: U11.49 (IOB_81_GBIN5); also elsewhere on the board
FT_D0: U11.37 (IOB_56); also elsewhere on the board
FT_D1: U11.38 (IOB_57); also elsewhere on the board
FT_D2: U11.39 (IOB_61); also elsewhere on the board
FT_D3: U11.41 (IOB_63); also elsewhere on the board
FT_D4: U11.42 (IOB_64); also elsewhere on the board
FT_D5: U11.43 (IOB_71); also elsewhere on the board
FT_D6: U11.44 (IOB_72); also elsewhere on the board
FT_D7: U11.45 (IOB_73); also elsewhere on the board
FT_OE_N: U11.60 (IOB_95); also elsewhere on the board
FT_RD_N: U11.52 (IOB_82_GBIN4); also elsewhere on the board
FT_RXF_N: U11.47 (IOB_79); also elsewhere on the board
FT_SIWU_N: U11.56 (IOB_94); also elsewhere on the board
FT_TXE_N: U11.48 (IOB_80); also elsewhere on the board
FT_WR_N: U11.55 (IOB_91); also elsewhere on the board
GND: C44.2, C45.2, C46.2, C47.2, C48.2, C49.2, C50.2, C51.2, C52.2, C53.2, C54.2, C55.2, C56.2, C57.2, C58.2, C59.2, C60.2, C61.2, C62.2, D4.1 (K), D5.1 (K), J4.2, U11.5 (GND), U11.13 (GND), U11.14 (GND), U11.53 (GNDPLL0), U11.59 (GND), U11.69 (GND), U11.86 (GND), U11.103 (GND), U11.127 (GNDPLL1), U11.132 (GND), U11.140 (GND), U12.4 (GND); also elsewhere on the board
SD_A0: U11.64 (IOB_104_CBSEL1); also elsewhere on the board
SD_A1: U11.63 (IOB_103_CBSEL0); also elsewhere on the board
SD_A2: U11.62 (IOB_102); also elsewhere on the board
SD_A3: U11.61 (IOB_96); also elsewhere on the board
SD_A4: U11.74 (IOR_110); also elsewhere on the board
SD_A5: U11.76 (IOR_112); also elsewhere on the board
SD_A6: U11.78 (IOR_114); also elsewhere on the board
SD_A7: U11.80 (IOR_116); also elsewhere on the board
SD_A8: U11.82 (IOR_118); also elsewhere on the board
SD_A9: U11.83 (IOR_119); also elsewhere on the board
SD_A10: U11.73 (IOR_109); also elsewhere on the board
SD_A11: U11.85 (IOR_128); also elsewhere on the board
SD_BA0: U11.79 (IOR_115); also elsewhere on the board
SD_BA1: U11.75 (IOR_111); also elsewhere on the board
SD_CAS_N: U11.87 (IOR_136); also elsewhere on the board
SD_CKE: U11.88 (IOR_137); also elsewhere on the board
SD_CLK_S: U11.91 (IOR_139); also elsewhere on the board
SD_CS_N: U11.81 (IOR_117); also elsewhere on the board
SD_DQ0: U11.115 (IOT_172); also elsewhere on the board
SD_DQ1: U11.114 (IOT_171); also elsewhere on the board
SD_DQ2: U11.113 (IOT_170); also elsewhere on the board
SD_DQ3: U11.110 (IOT_168); also elsewhere on the board
SD_DQ4: U11.106 (IOR_166); also elsewhere on the board
SD_DQ5: U11.102 (IOR_161); also elsewhere on the board
SD_DQ6: U11.99 (IOR_152); also elsewhere on the board
SD_DQ7: U11.96 (IOR_146); also elsewhere on the board
SD_DQ8: U11.95 (IOR_144); also elsewhere on the board
SD_DQ9: U11.97 (IOR_147); also elsewhere on the board
SD_DQ10: U11.98 (IOR_148); also elsewhere on the board
SD_DQ11: U11.101 (IOR_160); also elsewhere on the board
SD_DQ12: U11.104 (IOR_164); also elsewhere on the board
SD_DQ13: U11.105 (IOR_165); also elsewhere on the board
SD_DQ14: U11.107 (IOR_167); also elsewhere on the board
SD_DQ15: U11.112 (IOT_169); also elsewhere on the board
SD_LDQM: U11.94 (IOR_141_GBIN2); also elsewhere on the board
SD_RAS_N: U11.84 (IOR_120); also elsewhere on the board
SD_UDQM: U11.93 (IOR_140_GBIN3); also elsewhere on the board
SD_WE_N: U11.90 (IOR_138); also elsewhere on the board
VCCPLL0: C58.1, C59.1, R25.2, U11.54 (VCCPLL0)
VCCPLL1: C60.1, C61.1, R26.2, U11.126 (VCCPLL1)

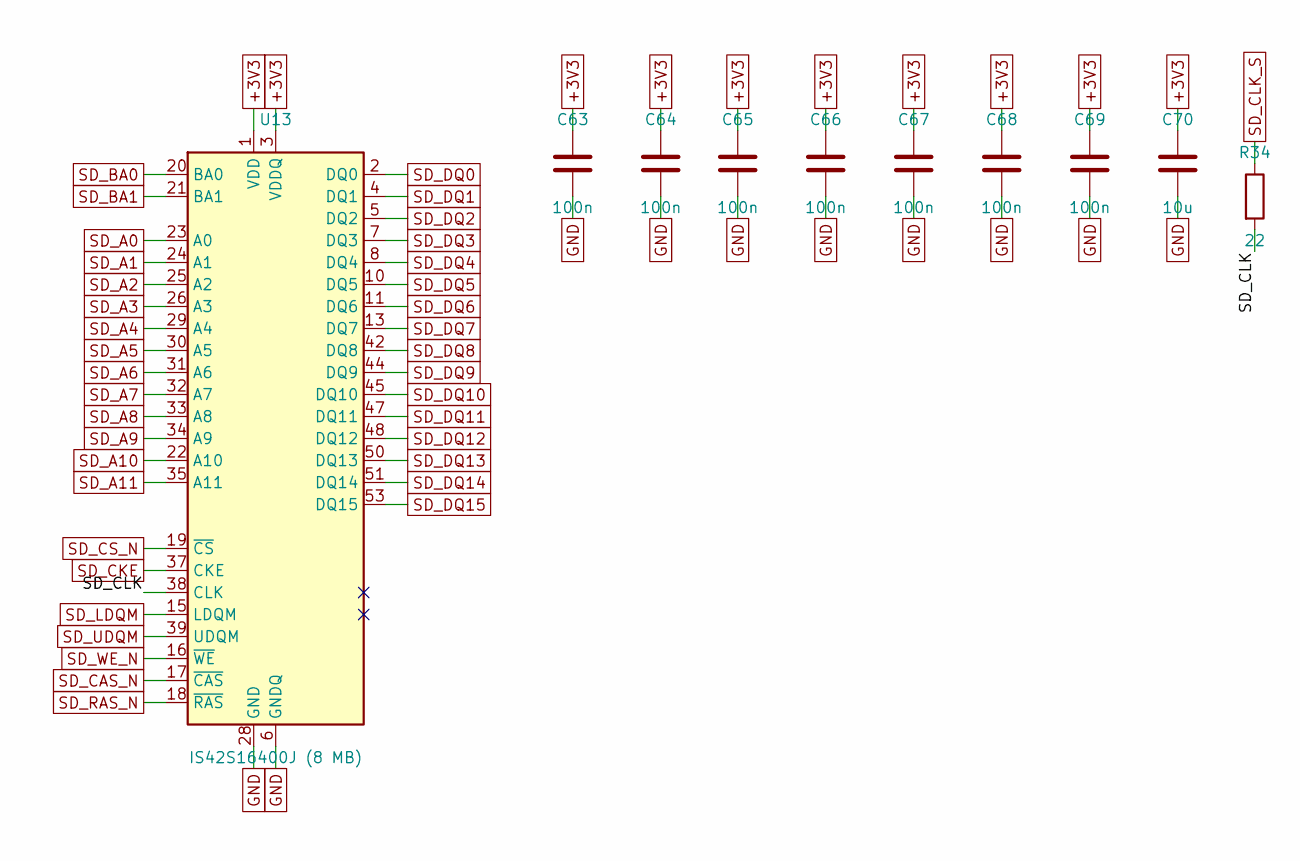
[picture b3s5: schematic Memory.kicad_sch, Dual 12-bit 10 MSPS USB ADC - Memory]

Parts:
C63, C64, C65, C66, C67, C68, C69: 100n; C_0603_1608Metric
C70: 10u; C_0805_2012Metric
R34: 22; R_0603_1608Metric
U13: IS42S16400J (8 MB); TSOP-II-54_22.2x10.16mm_P0.8mm

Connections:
+3V3: C63.1, C64.1, C65.1, C66.1, C67.1, C68.1, C69.1, C70.1, U13.1 (VDD), U13.3 (VDDQ), U13.9 (VDDQ), U13.14 (VDD), U13.27 (VDD), U13.43 (VDDQ), U13.49 (VDDQ); also elsewhere on the board
/Memory/SD_CLK: R34.2, U13.38 (CLK)
GND: C63.2, C64.2, C65.2, C66.2, C67.2, C68.2, C69.2, C70.2, U13.6 (GNDQ), U13.12 (GNDQ), U13.28 (GND), U13.41 (GND), U13.46 (GNDQ), U13.52 (GNDQ), U13.54 (GND); also elsewhere on the board
SD_A0: U13.23 (A0); also elsewhere on the board
SD_A1: U13.24 (A1); also elsewhere on the board
SD_A2: U13.25 (A2); also elsewhere on the board
SD_A3: U13.26 (A3); also elsewhere on the board
SD_A4: U13.29 (A4); also elsewhere on the board
SD_A5: U13.30 (A5); also elsewhere on the board
SD_A6: U13.31 (A6); also elsewhere on the board
SD_A7: U13.32 (A7); also elsewhere on the board
SD_A8: U13.33 (A8); also elsewhere on the board
SD_A9: U13.34 (A9); also elsewhere on the board
SD_A10: U13.22 (A10); also elsewhere on the board
SD_A11: U13.35 (A11); also elsewhere on the board
SD_BA0: U13.20 (BA0); also elsewhere on the board
SD_BA1: U13.21 (BA1); also elsewhere on the board
SD_CAS_N: U13.17 (~CAS); also elsewhere on the board
SD_CKE: U13.37 (CKE); also elsewhere on the board
SD_CLK_S: R34.1; also elsewhere on the board
SD_CS_N: U13.19 (~CS); also elsewhere on the board
SD_DQ0: U13.2 (DQ0); also elsewhere on the board
SD_DQ1: U13.4 (DQ1); also elsewhere on the board
SD_DQ2: U13.5 (DQ2); also elsewhere on the board
SD_DQ3: U13.7 (DQ3); also elsewhere on the board
SD_DQ4: U13.8 (DQ4); also elsewhere on the board
SD_DQ5: U13.10 (DQ5); also elsewhere on the board
SD_DQ6: U13.11 (DQ6); also elsewhere on the board
SD_DQ7: U13.13 (DQ7); also elsewhere on the board
SD_DQ8: U13.42 (DQ8); also elsewhere on the board
SD_DQ9: U13.44 (DQ9); also elsewhere on the board
SD_DQ10: U13.45 (DQ10); also elsewhere on the board
SD_DQ11: U13.47 (DQ11); also elsewhere on the board
SD_DQ12: U13.48 (DQ12); also elsewhere on the board
SD_DQ13: U13.50 (DQ13); also elsewhere on the board
SD_DQ14: U13.51 (DQ14); also elsewhere on the board
SD_DQ15: U13.53 (DQ15); also elsewhere on the board
SD_LDQM: U13.15 (LDQM); also elsewhere on the board
SD_RAS_N: U13.18 (~RAS); also elsewhere on the board
SD_UDQM: U13.39 (UDQM); also elsewhere on the board
SD_WE_N: U13.16 (~WE); also elsewhere on the board
